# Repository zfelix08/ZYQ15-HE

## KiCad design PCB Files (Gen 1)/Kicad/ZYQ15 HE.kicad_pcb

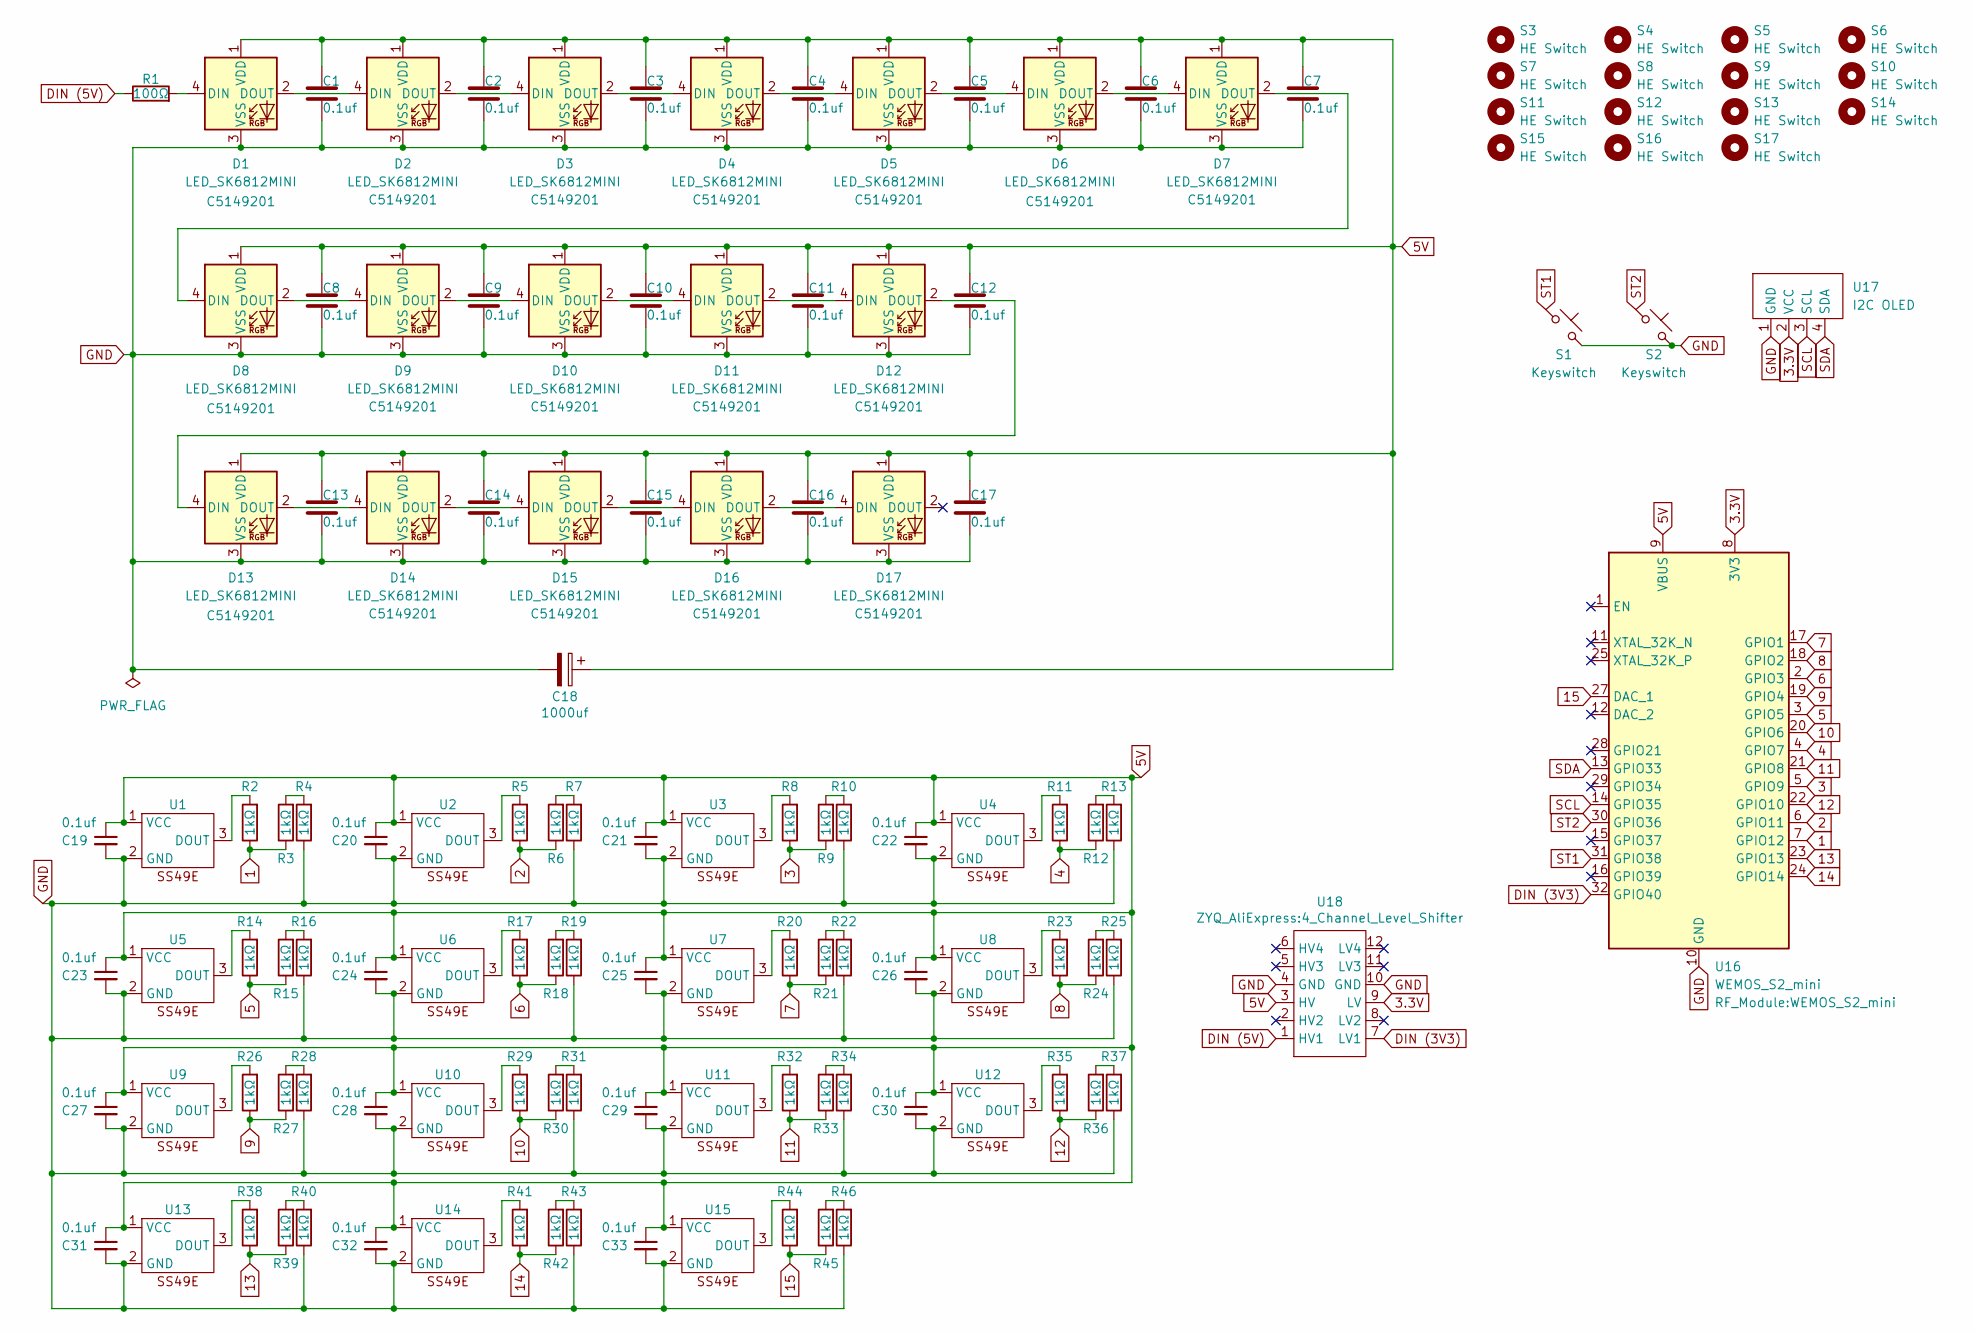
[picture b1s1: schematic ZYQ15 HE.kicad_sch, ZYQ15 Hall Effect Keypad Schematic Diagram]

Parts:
C1, C2, C3, C4, C5, C6, C7, C8, C9, C10, C11, C12, C13, C14, C15, C16, C17, C19, C20, C21, C22, C23, C24, C25, C26, C27, C28, C29, C30, C31, C32, C33: 0.1uf; C_1206_3216Metric_Pad1.33x1.80mm_HandSolder_BACK
C18: 1000uf; CP_Radial_D6.3mm_P2.50mm
D1, D2, D3, D4, D5, D6, D7, D8, D9, D10, D11, D12, D13, D14, D15, D16, D17: LED_SK6812MINI; LCSC C5149201
R1: 100Ω; R_Axial_DIN0207_L6.3mm_D2.5mm_P7.62mm_Horizontal
R2, R3, R4, R5, R6, R7, R8, R9, R10, R11, R12, R13, R14, R15, R16, R17, R18, R19, R20, R21, R22, R23, R24, R25, R26, R27, R28, R29, R30, R31, R32, R33, R34, R35, R36, R37, R38, R39, R40, R41, R42, R43, R44, R45, R46: 1kΩ; R_1206_3216Metric_Pad1.30x1.75mm_HandSolder_BACK
S1, S2: Keyswitch; Hotswap_MX_1.00u
S3, S4, S5, S6, S7, S8, S9, S10, S11, S12, S13, S14: HE Switch; MX_HE_PCB_1.00u
S15, S16, S17: HE Switch; MX_HE_PCB_1.25u
U1, U2, U3, U4, U5, U6, U7, U8, U9, U10, U11, U12, U13, U14, U15: SS49E_Back
U16: WEMOS_S2_mini
U17: I2C OLED; SSD1306_OLED_0.96in_BLACK
U18: 4_Channel_Level_Shifter

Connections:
1: R2.1, R3.1, U16.7 (GPIO12)
2: R5.1, R6.1, U16.6 (GPIO11)
3: R8.1, R9.1, U16.5 (GPIO9)
3.3V: U16.8 (3V3), U17.2 (VCC), U18.9 (LV)
4: R11.1, R12.1, U16.4 (GPIO7)
5: R14.1, R15.1, U16.3 (GPIO5)
5V: C1.1, C2.1, C3.1, C4.1, C5.1, C6.1, C7.1, C8.1, C9.1, C10.1, C11.1, C12.1, C13.1, C14.1, C15.1, C16.1, C17.1, C18.1, C19.1, C20.1, C21.1, C22.1, C23.1, C24.1, C25.1, C26.1, C27.1, C28.1, C29.1, C30.1, C31.1, C32.1, C33.1, D1.1 (VDD), D2.1 (VDD), D3.1 (VDD), D4.1 (VDD), D5.1 (VDD), D6.1 (VDD), D7.1 (VDD), D8.1 (VDD), D9.1 (VDD), D10.1 (VDD), D11.1 (VDD), D12.1 (VDD), D13.1 (VDD), D14.1 (VDD), D15.1 (VDD), D16.1 (VDD), D17.1 (VDD), U1.1 (VCC), U2.1 (VCC), U3.1 (VCC), U4.1 (VCC), U5.1 (VCC), U6.1 (VCC), U7.1 (VCC), U8.1 (VCC), U9.1 (VCC), U10.1 (VCC), U11.1 (VCC), U12.1 (VCC), U13.1 (VCC), U14.1 (VCC), U15.1 (VCC), U16.9 (VBUS), U18.3 (HV)
6: R17.1, R18.1, U16.2 (GPIO3)
7: R20.1, R21.1, U16.17 (GPIO1)
8: R23.1, R24.1, U16.18 (GPIO2)
9: R26.1, R27.1, U16.19 (GPIO4)
10: R29.1, R30.1, U16.20 (GPIO6)
11: R32.1, R33.1, U16.21 (GPIO8)
12: R35.1, R36.1, U16.22 (GPIO10)
13: R38.1, R39.1, U16.23 (GPIO13)
14: R41.1, R42.1, U16.24 (GPIO14)
15: R44.1, R45.1, U16.27 (DAC_1)
DIN (3V3): U16.32 (GPIO40), U18.7 (LV1)
DIN (5V): R1.1, U18.1 (HV1)
GND: C1.2, C2.2, C3.2, C4.2, C5.2, C6.2, C7.2, C8.2, C9.2, C10.2, C11.2, C12.2, C13.2, C14.2, C15.2, C16.2, C17.2, C18.2, C19.2, C20.2, C21.2, C22.2, C23.2, C24.2, C25.2, C26.2, C27.2, C28.2, C29.2, C30.2, C31.2, C32.2, C33.2, D1.3 (VSS), D2.3 (VSS), D3.3 (VSS), D4.3 (VSS), D5.3 (VSS), D6.3 (VSS), D7.3 (VSS), D8.3 (VSS), D9.3 (VSS), D10.3 (VSS), D11.3 (VSS), D12.3 (VSS), D13.3 (VSS), D14.3 (VSS), D15.3 (VSS), D16.3 (VSS), D17.3 (VSS), R4.1, R7.1, R10.1, R13.1, R16.1, R19.1, R22.1, R25.1, R28.1, R31.1, R34.1, R37.1, R40.1, R43.1, R46.1, S1.2, S2.2, U1.2 (GND), U2.2 (GND), U3.2 (GND), U4.2 (GND), U5.2 (GND), U6.2 (GND), U7.2 (GND), U8.2 (GND), U9.2 (GND), U10.2 (GND), U11.2 (GND), U12.2 (GND), U13.2 (GND), U14.2 (GND), U15.2 (GND), U16.10 (GND), U16.26 (GND), U17.1 (GND), U18.4 (GND), U18.10 (GND)
unnamed: D1.4 (DIN), R1.2
unnamed: D1.2 (DOUT), D2.4 (DIN)
unnamed: D2.2 (DOUT), D3.4 (DIN)
unnamed: D3.2 (DOUT), D4.4 (DIN)
unnamed: D4.2 (DOUT), D5.4 (DIN)
unnamed: D5.2 (DOUT), D6.4 (DIN)
unnamed: D6.2 (DOUT), D7.4 (DIN)
unnamed: D7.2 (DOUT), D8.4 (DIN)
unnamed: D8.2 (DOUT), D9.4 (DIN)
unnamed: D9.2 (DOUT), D10.4 (DIN)
unnamed: D10.2 (DOUT), D11.4 (DIN)
unnamed: D11.2 (DOUT), D12.4 (DIN)
unnamed: D12.2 (DOUT), D13.4 (DIN)
unnamed: D13.2 (DOUT), D14.4 (DIN)
unnamed: D14.2 (DOUT), D15.4 (DIN)
unnamed: D15.2 (DOUT), D16.4 (DIN)
unnamed: D16.2 (DOUT), D17.4 (DIN)
unnamed: R3.2, R4.2
unnamed: R6.2, R7.2
unnamed: R9.2, R10.2
unnamed: R12.2, R13.2
unnamed: R15.2, R16.2
unnamed: R18.2, R19.2
unnamed: R21.2, R22.2
unnamed: R24.2, R25.2
unnamed: R27.2, R28.2
unnamed: R30.2, R31.2
unnamed: R33.2, R34.2
unnamed: R36.2, R37.2
unnamed: R39.2, R40.2
unnamed: R42.2, R43.2
unnamed: R45.2, R46.2
unnamed: R2.2, U1.3 (DOUT)
unnamed: R5.2, U2.3 (DOUT)
unnamed: R8.2, U3.3 (DOUT)
unnamed: R11.2, U4.3 (DOUT)
unnamed: R14.2, U5.3 (DOUT)
unnamed: R17.2, U6.3 (DOUT)
unnamed: R20.2, U7.3 (DOUT)
unnamed: R23.2, U8.3 (DOUT)
unnamed: R26.2, U9.3 (DOUT)
unnamed: R29.2, U10.3 (DOUT)
unnamed: R32.2, U11.3 (DOUT)
unnamed: R35.2, U12.3 (DOUT)
unnamed: R38.2, U13.3 (DOUT)
unnamed: R41.2, U14.3 (DOUT)
unnamed: R44.2, U15.3 (DOUT)
SCL: U16.14 (GPIO35), U17.3 (SCL)
SDA: U16.13 (GPIO33), U17.4 (SDA)
ST1: S1.1, U16.31 (GPIO38)
ST2: S2.1, U16.30 (GPIO36)

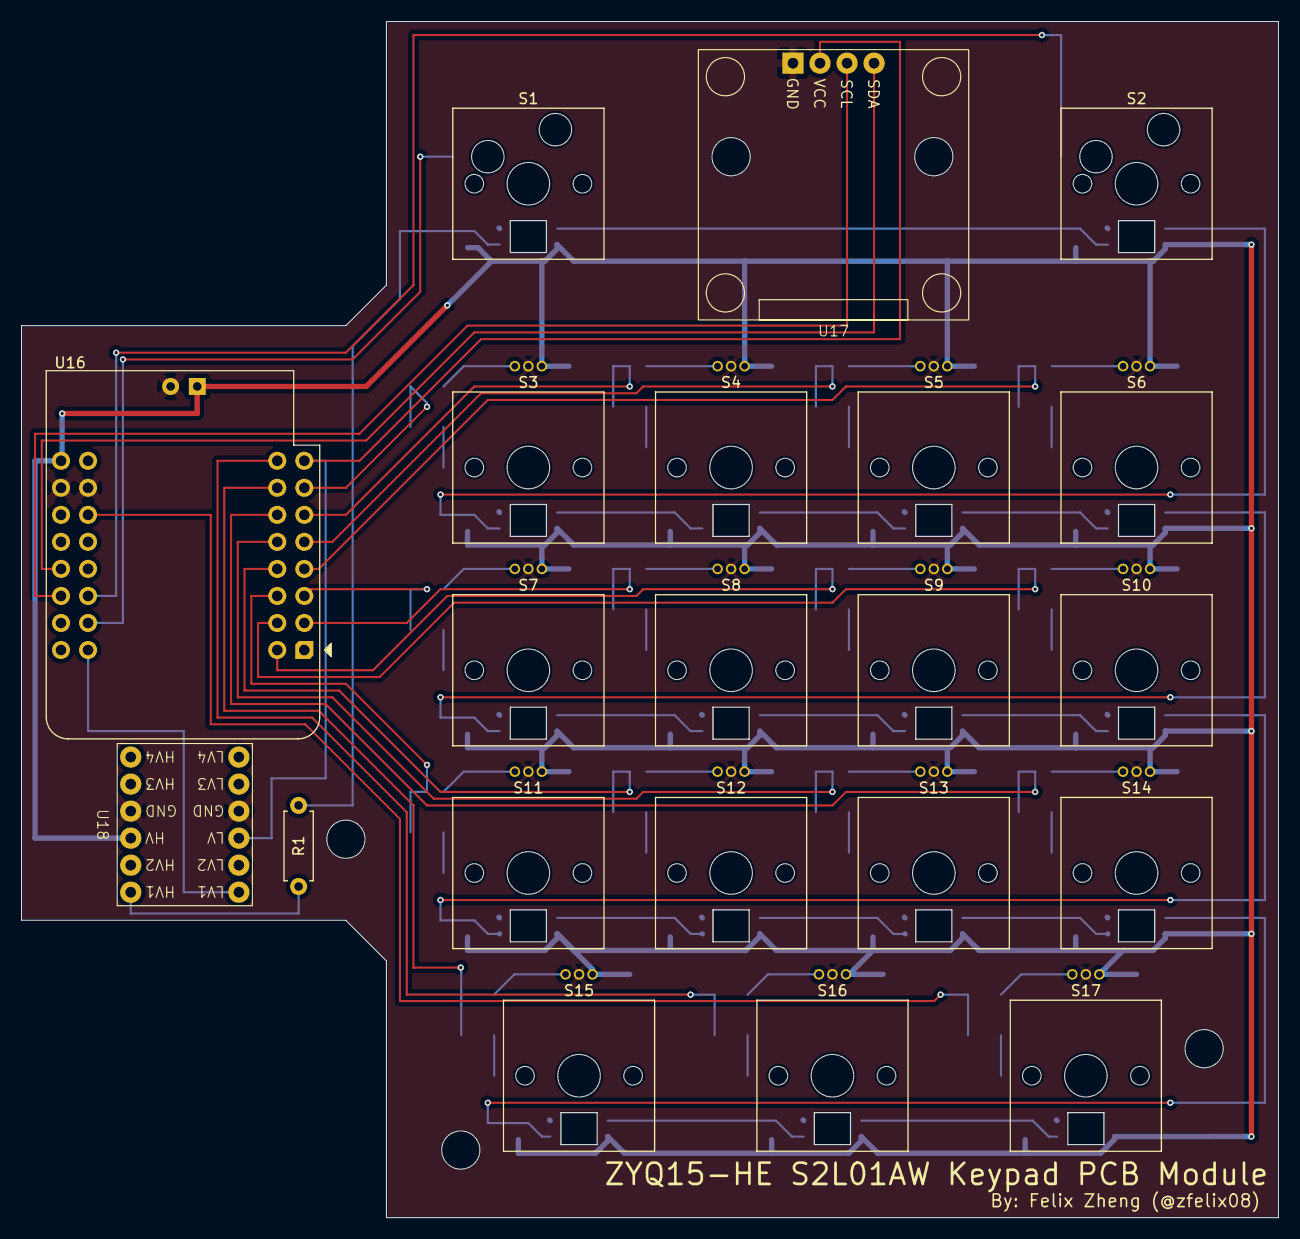
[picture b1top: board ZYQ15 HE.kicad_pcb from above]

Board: 2 copper layers, 118.1 x 112.4 mm, 131 parts (1 on the bottom side), 71 nets.

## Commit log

2025-04-23 Add .gitignore
2025-04-24 Add KiCAD project files
2025-04-27 Updated PCB Design files
2025-04-28 Finalized PCB files
    Included are the gerber and step files for the PCB
2025-04-28 Update .step file
2025-05-15 Update PCB/Enclosure Files
2025-05-16 Add .stl files
2025-06-26 Add 3D and PCB Files
2025-07-19 Restructure PCB and PlatformIO project directories
    Renamed 'PCB Files/Generation 1' to 'PCB Files (Gen 1)' and moved all related files accordingly. Added new PlatformIO project under 'PlatformIO Code (Gen 1)' with initial configuration, source, and d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
